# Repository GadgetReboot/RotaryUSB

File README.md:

# RotaryUSB
LS30 Rotary Joystick to USB Interface

  Required Arduino libraries, board files, and utilities:<br>
 <br>
  Before the ATTiny85 can be programmed with the sketch from the IDE, the Micronucleus bootloader must be flashed <br>
  with the ATTiny85 on a breadboard and using an Uno as a programmer (or some other method).<br>
  Once that is done and the ATTiny85 is installed on the USB PCB, it will appear as a USB device when plugged in and <br>
  the IDE can program it over USB.<br>
 <br>
  Download Micronucleus bootloader v2.4 file t85_default.hex from<br>
  https://github.com/ArminJo/micronucleus-firmware/tree/ca7216847e6bbf695067076b6c07703ca2d96761/firmware/releases<br>
 <br>
  To upload t85_default.hex bootloader, an Arduino Uno can be used as an ISP programmer to program an ATTiny85<br>
  on a breadboard. A wiring diagram can be found here as a reference<br>
  https://homemadehardware.com/guides/programming-an-attiny85/<br>
  but just use that site as a wiring example between the Uno programmer and the ATTiny85 on a breadboard.<br>
  Setup the Uno as a programmer by loading the IDE example sketch &quot;ArduinoISP&quot; (which comes with the IDE) <br>
  and program the Uno. Now the Uno can act as a programmer between the computer and the ATTiny chip.<br>
  Add a capacitor (around 1 to 10 uF) between the Uno Reset and Ground pins (capacitor + to Reset and - to Gnd)<br>
  This prevents the Uno from getting reset by the computer when attempting to program the ATTiny.<br>
  Then wire up the connections between Uno and ATTiny85 to flash the bootloader with the following instructions.<br>
 <br>
  This example procedure was done on Windows 10. Similar instructions can be found for Linux/Mac by following the<br>
  general process and using the equivalent versions of tools available on the other OS. <br>
 <br>
  Download avrdude.conf and avrdude.exe from<br>
  https://github.com/ArminJo/micronucleus-firmware/tree/ca7216847e6bbf695067076b6c07703ca2d96761/windows_exe<br>
  Place the avrdude files in the same folder as the previously downloaded micronucleus bootloader file t85_default.hex<br>
  Also place the flash_bootloader.bat file from the github project https: github.com/GadgetReboot/RotaryUSB in the same folder.<br>
  Run flash_bootloder.bat and it will launch avrdude with the settings needed to flash t85_default.hex into the ATTiny85<br>
  A commandline parameter is needed to specify the com port of the Uno being used as a programmer.<br>
  That will be the same COM port that was used in the IDE to set the Uno as a programmer.<br>
  example of a valid command line: flash_bootloader.bat COM1<br>
  If the programming fails but the wiring seems good, it's possible the fuses in the ATTiny need to be reset if the<br>
  chip was previously configured to disable the reset pin and use it as a GPIO. Reset is needed for programming<br>
  so either a different chip should be used, or a high voltage programmer must be used to reset the fuses and <br>
  allow programming again. <br>
  Example fuse reset procedure: https: www.youtube.com/watch?v=JskwC4bhgx4<br>
 <br>
  With the ATTiny85 programmed with a bootloader, the Uno programmer is no longer needed.<br>
  Plug the ATTiny85 into the USB board and plug it into a USB port on a computer.<br>
  If the device doesn't show up, <br>
  Windows drivers may need to be installed to recognize the board as a USB device.<br>
  The ones that worked in this Windows 10 example were<br>
  https://github.com/digistump/DigistumpArduino/releases/download/1.6.7/Digistump.Drivers.zip<br>
  DPinst64.exe was run, which installed drivers and allowed the ATTiny85 board to appear as a USB Keyboard<br>
  when the sketch was flashed.<br>
 <br>
  When the USB board is ready to be programmed with the sketch over USB with the Arduino IDE,<br>
  Tested with Arduino IDE 2.3.3 on Windows 10 using:<br>
  Micronucleus bootloader 2.4 t85_default.hex flashed to ATTiny85 using avrdude tool, run with flash_bootloader.bat<br>
  Install Arduino IDE Bounce2 library 2.1 (some newer versions may not compile for some reason)<br>
  Install Arduino IDE Board Manager: Digistump AVR Boards 1.6.7 to add Digispark board support:<br>
  Add url to Arduino preferences/additional board URLs <br>
  https://raw.githubusercontent.com/digistump/arduino-boards-index/master/package_digistump_index.json<br>
  Then in the Tools menu to add board support, search for the Digistump AVR 1.6.7 board file and install it<br>
  With this sketch open, choose the target board Digispark Default 16.5 MHz from the Tools menu.<br>
  no other options should be needed from the Tools menu to configure the project for uploading<br>
 <br>
  Now the sketch should compile and upload.<br>
  Note that the board should be unplugged prior to starting a sketch upload from the IDE. <br>
  The IDE will say when it is time to plug in the USB board (with a 60 second timeout) and it will program it.<br>
  It may take a few seconds for the OS to detect the USB device before the IDE can program it.<br>
 <br>
  After programming, if the board is power cycled, it should appear as a USB keyboard and the rotating<br>
  joystick should produce keystrokes when moved. The keystrokes can be changed within the sketch, especially<br>
  if two boards are used on the same computer for 2 player games.<br>
  Each board should have unique keystrokes assigned and when both are plugged into the same computer, <br>
  they should behave like the same keyboard, just sending different keys.

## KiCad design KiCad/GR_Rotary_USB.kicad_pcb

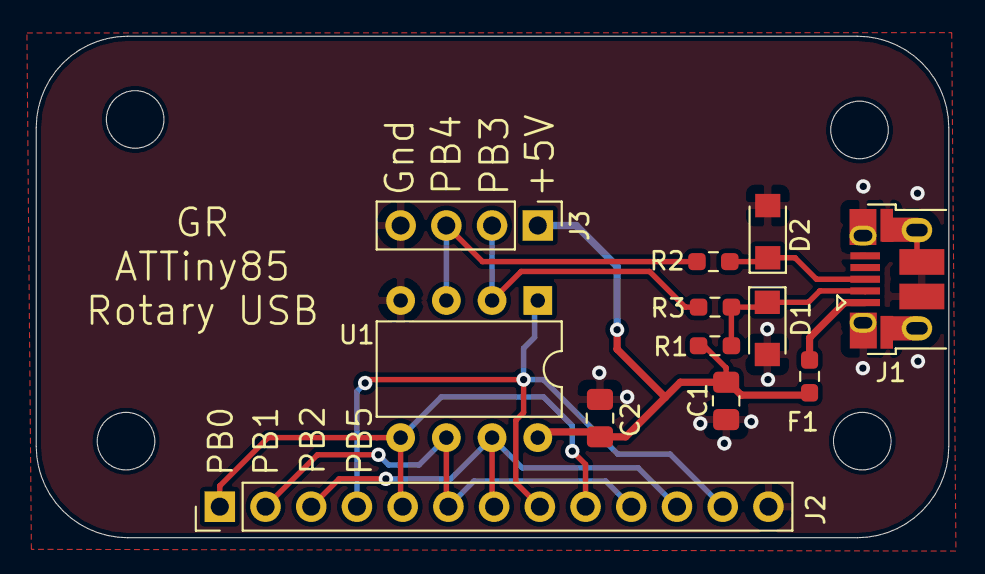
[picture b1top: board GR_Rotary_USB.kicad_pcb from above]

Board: 2 copper layers, 50.7 x 27.9 mm, 16 parts (0 on the bottom side), 11 nets.

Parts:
C1: 4.7uF; C_0805_2012Metric_Pad1.18x1.45mm_HandSolder
C2: 100nF; C_0805_2012Metric_Pad1.18x1.45mm_HandSolder
D1, D2: 3.6v Zener; D_SMF
F1: MF-FSMF050X; R_0603_1608Metric_Pad0.98x0.95mm_HandSolder
J1: USB_B_Micro; USB_Micro-B_Amphenol_10103594-0001LF_Horizontal
J2: Rotary Joystick; PinHeader_1x13_P2.54mm_Vertical
J3: Access Pins; PinHeader_1x04_P2.54mm_Vertical
MH1, MH2, MH3, MH4: MountingHole; MountingHole_3.2mm_M3
R1: 1.5K; R_0603_1608Metric_Pad0.98x0.95mm_HandSolder
R2, R3: 66.5r; R_0603_1608Metric_Pad0.98x0.95mm_HandSolder
U1: ATtiny85-20PU; DIP-8_W7.62mm

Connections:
+5V: C1.1, C2.1, F1.1, J3.1, R1.1, U1.8
/DM: D1.1, J1.2, R1.2, R3.2
/DP: D2.1, J1.3, R2.2
/PB0: J2.1, J2.5, J2.9, U1.5
/PB1: J2.2, J2.6, J2.10, U1.6
/PB2: J2.3, J2.7, J2.11, U1.7
/PB3: J3.2, R3.1, U1.2
/PB4: J3.3, R2.1, U1.3
/PB5: J2.4, J2.8, J2.12, U1.1
GNDREF: C1.2, C2.2, D1.2, D2.2, J1.5, J1.6, J2.13, J3.4, U1.4
unnamed: F1.2, J1.1
